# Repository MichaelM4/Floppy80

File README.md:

########################################################################

Floppy 80 for the TRS-80 Model 3/4 NGA

The Floppy80 emulates up to four floppy drives.

Configuration of the Floppy80 is performed with the placement of
files on the SD-Card inserted in its card reader.
The files are as follows:

boot.cfg
- specified the defaul ini file to load at reset of the Floppy80
  when the floppy 80 boots or is reset it reads the contents of
  the boot.cfg to determine the default configuration ini file.

ini files
- specifies the disk images to load after reset.

  ini options
  - Drive0 - specified the image to load for drive :0
  - Drive1 - specified the image to load for drive :1
  - Drive2 - specified the image to load for drive :2
  - Drive3 - specified the image to load for drive :3

dmk files
- these are virtual disk images with a specific file format
  that allows them to be generated and used with a number
  of existing programs and simulators.

hfe files
- these are virtual disk images with a specific file format
  that allows them to be generated and used with a number
  of existing programs and simulators.

########################################################################

FDC utility
- Is a utility to interact with the Floppy80 from within the
  TRS-80 Model 3/4 operating environment.  Versions of FDC exist
  for the following operating systems

  - CPM
  - LDOS
  - TRSDOS

  FDC.COM is used with the CP/M OS and
  FDC/CMD is used with the rest.

  Usage

  FDC OPT PARM1:drive

  Where:
  - OPT is one of the following
    - STA - returns the status of the Floppy80.
    - INI - switches between tyhe differnt ini file on the SD-Card.
    - DMK - allows the mounting of DMK disk images in the root folder
            of the SD-Card for a specified drive (0, 1, 2 or 3).
    - IMP - imports a file from the root folder of the SD-Card
            into one of the mounted disk images (0, 1, 2 or 3).

  FDC STA
  - Displays the contects to the ini file specified by boot.cfg

  FDC INI filename.exe
  - filename.exe is optional.  If not specified and list of ini files
    on the SD-Card will be displayed allow you to select the one to
    write to boot.cfg.  When specified FDC will bypass the file
    selection process.

  FDC DMK filename.exe n
  - filename.exe:n is optional.  When specified it will mount
    the dmk file names by filename.exe into the drive specified
    by n.  For example

    FDC DMK LDOS-DATA.DMK 2

    will mount the dmk file LDOS-DATA.DMK into drive :2

    If filename.exe:n is not specfied a list of dmk files
    will be listed allowing you to select on and the drive
    to mount it into.

  FDC IMP filename.exe:n
  - imports the specified file from the root folder of the
    FAT32 formated SD-Card to the disk image indicated by n.

########################################################################

Building Source
- Floppy80 firmware
  - Uses VSCode and the Pi Pico extension.

- FDC TRS (utility for the TRSDOS related utility)
  
  - zmac fdc.asm

- FDC CP/M (utility for the CP/M related utility)
  1. Import the source file onto a working CP/M diskette.
  
       D:\TRS-80\TRSUtils\trswrite cpm-work2.dmk -o fdc.c
     
  2. Run TRS80GP loading the CP/M disk images.
     
       start trs80gp -m4 -vs -frehd -frehd_dir source -turbo -mem 128 -d0 M4-CPM-MONTEZUMA-v22.dmk -d1 cpm-hc-disk.dmk -d2 cpm-work1.dmk -d3 cpm-work2.dmk
     
  3. Compile the C source using the Hi-Tech C compilier.

     b:
     c d:fdc.c

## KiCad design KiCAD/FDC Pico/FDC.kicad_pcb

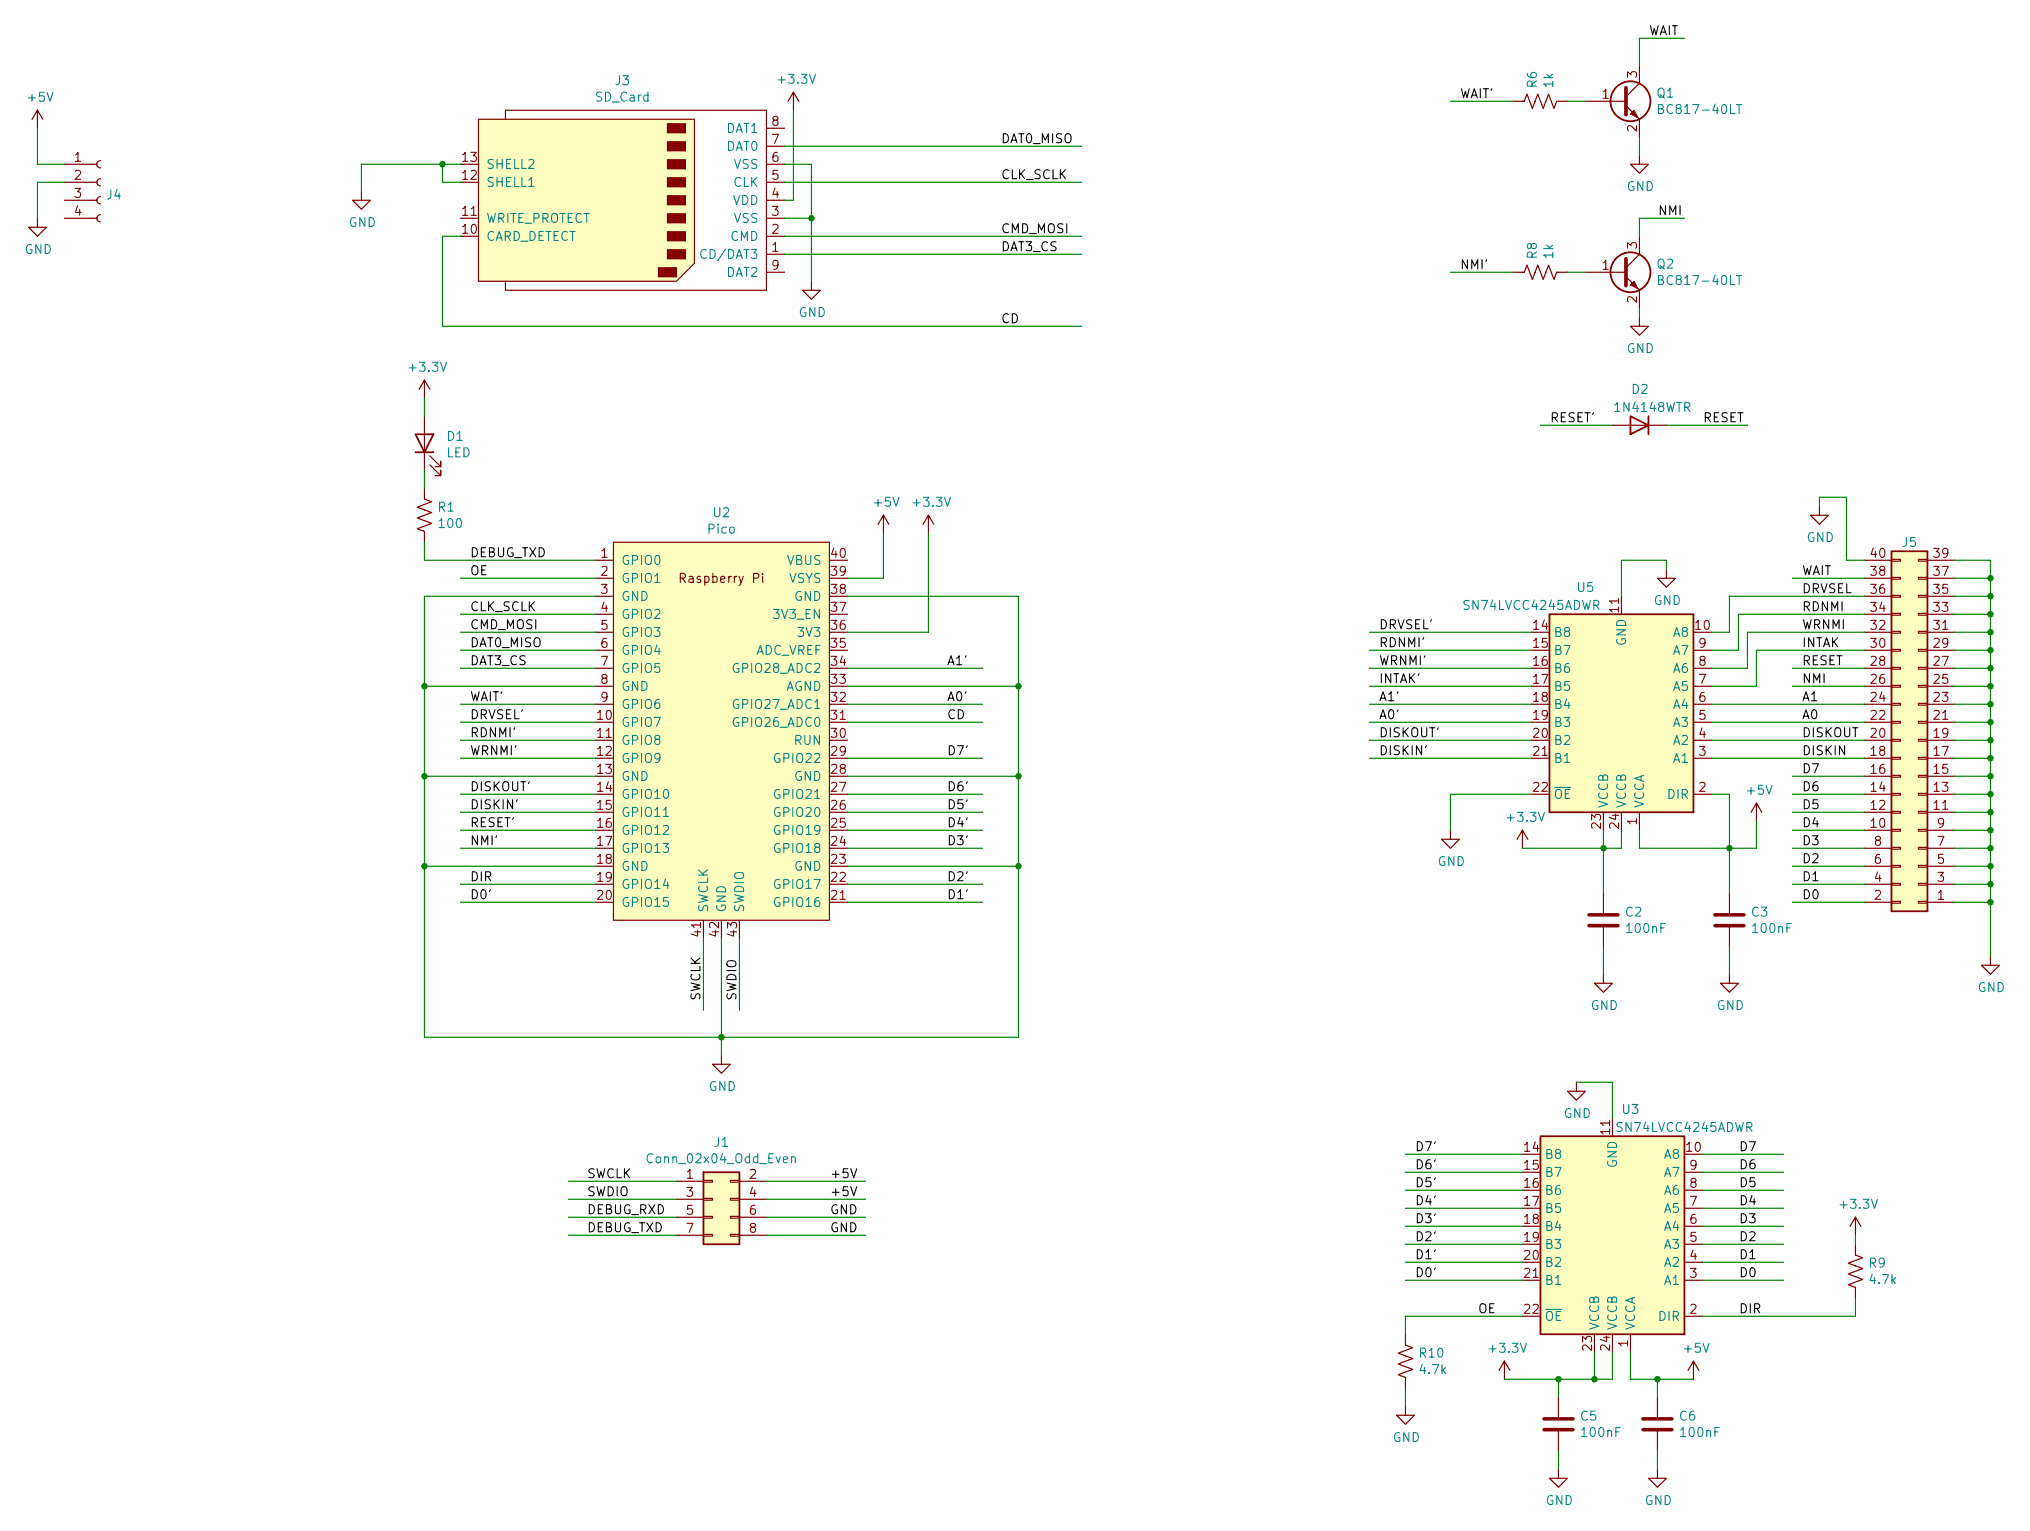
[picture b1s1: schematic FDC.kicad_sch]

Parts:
C2, C3, C5, C6: 100nF; C_0603_1608Metric_Pad1.08x0.95mm_HandSolder; Digikey 732-8080-1-ND
D1: LED; LED_2816_7142Metric_Pad3.20x4.45mm_HandSolder; Digikey 754-1519-1-ND
D2: 1N4148WTR; D_1206_3216Metric_Pad1.42x1.75mm_HandSolder; Digikey 1655-1360-1-ND
J1: Conn_02x04_Odd_Even; IDC-Header_2x04_P2.54mm_Vertical
J3: SD_Card; SD_Kyocera_145638109511859+; Digikey 478-4058-1-ND
J4: Conn_01x04_Female; TE_MATE-N-LOK_350211-1_1x04_P5.08mm_Horizontal; Digikey A25430-ND
J5: Conn_02x20_Odd_Even; PinHeader_2x20_P2.54mm_Vertical; Digikey ED10529-ND
Q1: BC817-40LT; SOT-23_Handsoldering; Digikey BC817-40LT3GOSCT-ND
Q2: BC817-40LT; SOT-23_Handsoldering; Digikey BC817-40FDICT-ND
R1: 100; R_0805_2012Metric_Pad1.20x1.40mm_HandSolder; Digikey RMCF0805FT100RCT-ND
R6, R8: 1k; R_0805_2012Metric_Pad1.20x1.40mm_HandSolder; Digikey A106056CT-ND
R9, R10: 4.7k; R_0805_2012Metric_Pad1.20x1.40mm_HandSolder; Digikey A129757CT-ND
U2: Pico; RPi_Pico_SMD_TH; Digikey 2648-SC0915CT-ND
U3, U5: SN74LVCC4245ADWR; SOIC-24W_7.5x15.4mm_P1.27mm; Digikey 296-26634-1-ND

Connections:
+3V3: C2.1, C5.1, D1.2 (A), J3.4 (VDD), R9.1, U2.36 (3V3), U3.23 (VCCB), U3.24 (VCCB), U5.23 (VCCB), U5.24 (VCCB)
+5V: C3.1, C6.1, J1.2, J1.4, J4.1, U2.39 (VSYS), U3.1 (VCCA), U5.1 (VCCA), U5.2 (DIR)
/A0: J5.22, U5.5 (A3)
/A0': U2.32 (GPIO27_ADC1), U5.19 (B3)
/A1: J5.24, U5.6 (A4)
/A1': U2.34 (GPIO28_ADC2), U5.18 (B4)
/CD: J3.10 (CARD_DETECT), U2.31 (GPIO26_ADC0)
/CLK_SCLK: J3.5 (CLK), U2.4 (GPIO2)
/CMD_MOSI: J3.2 (CMD), U2.5 (GPIO3)
/D0: J5.2, U3.3 (A1)
/D0': U2.20 (GPIO15), U3.21 (B1)
/D1: J5.4, U3.4 (A2)
/D1': U2.21 (GPIO16), U3.20 (B2)
/D2: J5.6, U3.5 (A3)
/D2': U2.22 (GPIO17), U3.19 (B3)
/D3: J5.8, U3.6 (A4)
/D3': U2.24 (GPIO18), U3.18 (B4)
/D4: J5.10, U3.7 (A5)
/D4': U2.25 (GPIO19), U3.17 (B5)
/D5: J5.12, U3.8 (A6)
/D5': U2.26 (GPIO20), U3.16 (B6)
/D6: J5.14, U3.9 (A7)
/D6': U2.27 (GPIO21), U3.15 (B7)
/D7: J5.16, U3.10 (A8)
/D7': U2.29 (GPIO22), U3.14 (B8)
/DAT0_MISO: J3.7 (DAT0), U2.6 (GPIO4)
/DAT3_CS: J3.1 (CD/DAT3), U2.7 (GPIO5)
/DEBUG_TXD: J1.7, R1.2, U2.1 (GPIO0)
/DIR: R9.2, U2.19 (GPIO14), U3.2 (DIR)
/DISKIN: J5.18, U5.3 (A1)
/DISKIN': U2.15 (GPIO11), U5.21 (B1)
/DISKOUT: J5.20, U5.4 (A2)
/DISKOUT': U2.14 (GPIO10), U5.20 (B2)
/DRVSEL: J5.36, U5.10 (A8)
/DRVSEL': U2.10 (GPIO7), U5.14 (B8)
/INTAK: J5.30, U5.7 (A5)
/NMI: J5.26, Q2.3 (C)
/NMI': R8.1, U2.17 (GPIO13)
/OE: R10.1, U2.2 (GPIO1), U3.22 (~OE)
/RDNMI: J5.34, U5.9 (A7)
/RDNMI': U2.11 (GPIO8), U5.15 (B7)
/RESET: D2.1 (K), J5.28
/RESET': D2.2 (A), U2.16 (GPIO12)
/SWCLK: J1.1, U2.41 (SWCLK)
/SWDIO: J1.3, U2.43 (SWDIO)
/WAIT: J5.38, Q1.3 (C)
/WAIT': R6.1, U2.9 (GPIO6)
/WRNMI: J5.32, U5.8 (A6)
/WRNMI': U2.12 (GPIO9), U5.16 (B6)
GND: C2.2, C3.2, C5.2, C6.2, J1.6, J1.8, J3.3 (VSS), J3.6 (VSS), J3.12 (SHELL1), J3.13 (SHELL2), J4.2, J5.1, J5.3, J5.5, J5.7, J5.9, J5.11, J5.13, J5.15, J5.17, J5.19, J5.21, J5.23, J5.25, J5.27, J5.29, J5.31, J5.33, J5.35, J5.37, J5.39, J5.40, Q1.2 (E), Q2.2 (E), R10.2, U2.3 (GND), U2.8 (GND), U2.13 (GND), U2.18 (GND), U2.23 (GND), U2.28 (GND), U2.33 (AGND), U2.38 (GND), U2.42 (GND), U3.11 (GND), U3.12 (GND), U3.13 (GND), U5.11 (GND), U5.12 (GND), U5.13 (GND), U5.22 (~OE)
unnamed: D1.1 (K), R1.1
unnamed: Q1.1 (B), R6.2
unnamed: Q2.1 (B), R8.2

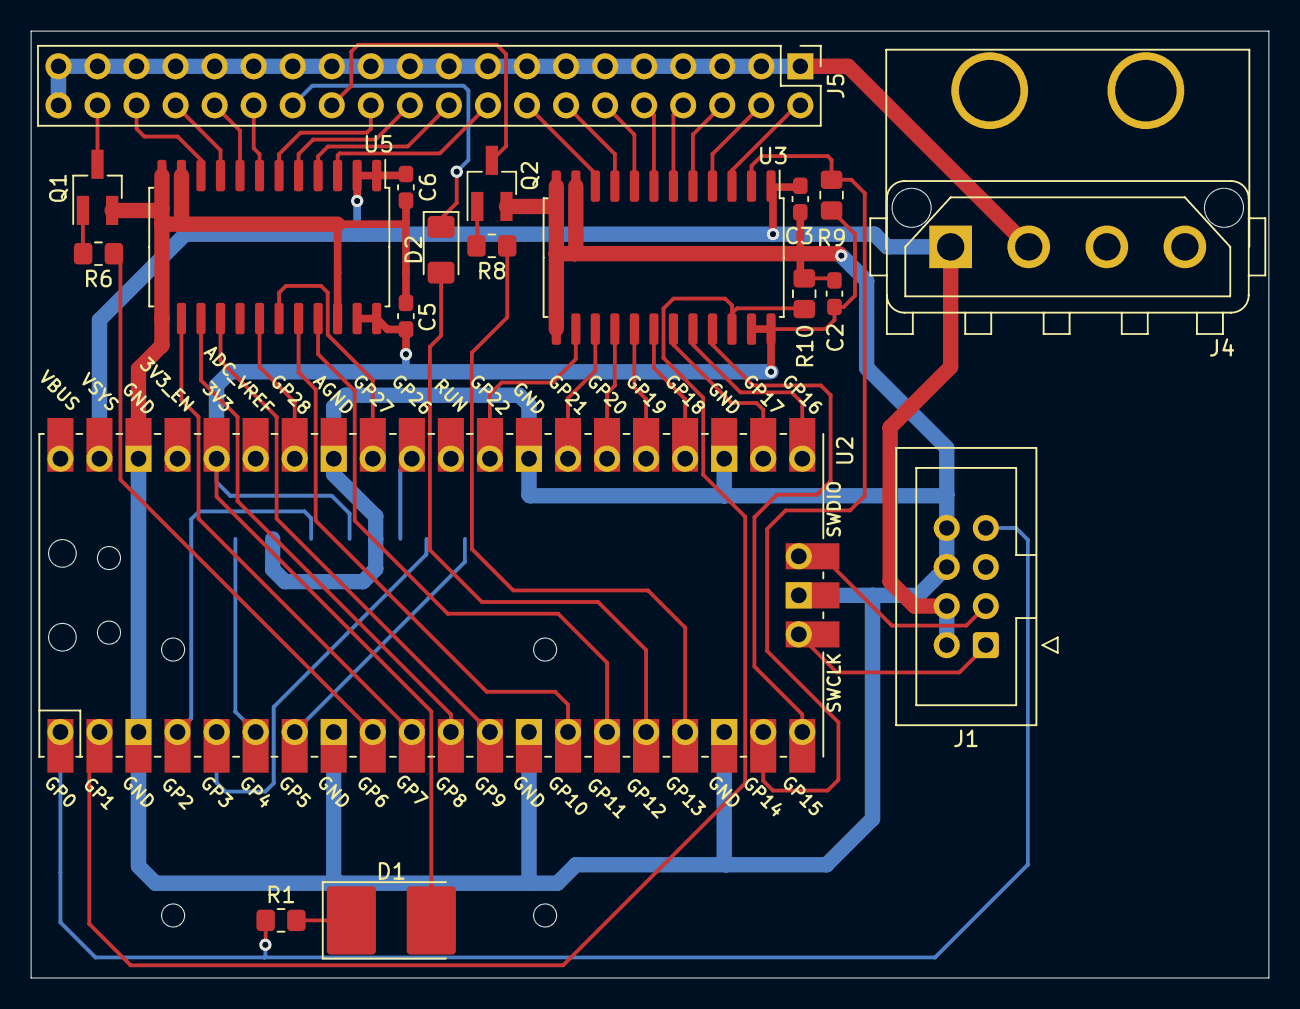
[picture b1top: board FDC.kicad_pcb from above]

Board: 2 copper layers, 80.5 x 61.6 mm, 20 parts (1 on the bottom side), 53 nets.

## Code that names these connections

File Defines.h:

#ifndef _H_DEFINES_
#define _H_DEFINES_

#include <stdio.h>

// set to 1 to enable capture of bus activity logging to sd-card
#define ENABLE_TRACE_LOG 0

///////////////////////////////////////////////////////////////////////////////////////////////////
// Bit - 31 30 29 28 27 26 25 24 23 22 21 20 19 18 17 16 15 14  13  12  11     10      9     8     7      6    5    4    3   2   1  0
// Net -          A1 A0 CD          D7 D6 D5 D4 D3 D2 D1 D0 DIR NMI RST DISKIN DISKOUT WRNMI RDNMI DRVSEL WAIT DAT3 DAT0 CMD CLK OE TXD
//       0  0  0  1  1  1  0  0  0  1  1  1  1  1  1  1  1  0   0   1   1      1       1     1     1      0    0    0    0   0   0  0
//       ----------  ----------  ----------  ----------  ------------   ----------------------     ------------------    ------------
// Hex            1           C           7           F             9                        F                      8               0
#define GPIO_IN_MASK 0x1C7F9F80

#define DRVSEL_MASK   0x00000080
#define RDNMI_MASK    0x00000100
#define WRNMI_MASK    0x00000200
#define DISKOUT_MASK  0x00000400
#define DISKIN_MASK   0x00000800

#define INTR_MASK     (DRVSEL_MASK | RDNMI_MASK | WRNMI_MASK | DISKOUT_MASK | DISKIN_MASK)

#define ADDRESS_MASK  0x18000000
#define DATA_BUS_MASK 0x007F8000

#define NMI_MASK      0x00002000
#define WAIT_MASK     0x00000040

#define RED_LED_PIN 0
#define OE_PIN      1
#define CLK_SCLK    2
#define CMD_MOSI    3
#define DAT0_MISO   4
#define DAT3_CS     5

#define WAIT_PIN    6
#define DRVSEL_PIN  7
#define RDNMI_PIN   8
#define WRNMI_PIN   9
#define DISKOUT_PIN 10
#define DISKIN_PIN  11

#define RESET_PIN   12
#define NMI_PIN     13
#define DIR_PIN     14

#define D0_PIN      15
#define D1_PIN      16
#define D2_PIN      17
#define D3_PIN      18
#define D4_PIN      19
#define D5_PIN      20
#define D6_PIN      21
#define D7_PIN      22

#define CD_PIN      26

#define A0_PIN      27
#define A1_PIN      28

#define DIR_PIN_MASK  0x4000

///////////////////////////////////////////////////////////////////////////////////////////////////

#define BOARD_REVISION 2

extern int g_nRevBoard;

///////////////////////////////////////////////////////////////////////////////////////////////////

// Low Power Timer Overflow Rates in Hz
#define TIMER_OVERFLOW_RATE				2000

///////////////////////////////////////////////////////////////////////////////////////////////////
// generic defines/equates

#ifndef TRUE
	#define FALSE	0
	#define TRUE	1
#endif

///////////////////////////////////////////////////////////////////////////////////////////////////
// typedefs

typedef long long          	INT64;
typedef unsigned long long 	UINT64;
typedef unsigned long      	UINT32;
typedef long               	INT32;
typedef unsigned short     	UINT16;
typedef short              	INT16;
typedef unsigned char		    UINT8;
typedef signed char        	INT8;
typedef signed char        	SCHAR;
typedef unsigned long      	DWORD;
typedef unsigned short     	WORD;
typedef unsigned char      	BYTE;
typedef char		       	    CHAR;

typedef struct {
   unsigned long long nSectorsTotal;
   unsigned long long nSectorsFree;
   unsigned long long nSectorSize;

   unsigned long nClustersTotal;
   unsigned long nClustersFree;
   unsigned long nClustersUsed;
   unsigned long nClustersBad;
   unsigned long nClusterSize;
} F_SPACE;

typedef union
{
  struct
  {
    // note that this is valid only if the GPIO all input is rotated down 6 bits
    // in reality WAIT is at GPIO6
    uint32_t WAIT:1;                     /*!< bit:  0      WAIT                               */
    uint32_t DVRSEL:1;                   /*!< bit:  1      DRIVESEL                           */
    uint32_t RDNMI:1;                    /*!< bit:  2      RDNMISTATUS                        */
    uint32_t WRNMI:1;                    /*!< bit:  3      WRNMIMASKREG                       */
    uint32_t DISK_OUT_WE:1;              /*!< bit:  4      DISK_OUT                           */
    uint32_t DISK_IN_RE:1;               /*!< bit:  5      DISK_IN                            */
    uint32_t RESET:1;                    /*!< bit:  6      RESET                              */
    uint32_t NMI:1;                      /*!< bit:  7      NMI                                */
    uint32_t DIR:1;                      /*!< bit:  8      DIR                                */
    uint32_t DATA:8;                     /*!< bit:  9..16  Data Bus                           */

    uint32_t NA2:3;                      /*!< bit:  17..19 NA                                 */
    uint32_t CD:1;                       /*!< bit:  20     CD                                 */
    uint32_t A0:1;                       /*!< bit:  21     A0                                 */
    uint32_t A1:1;                       /*!< bit:  22     A1                                 */

    uint32_t Count:9;                    /*!< bit:  23..31 Count                              */
  } b;                                   /*!< Structure used for bit  access                  */
  uint32_t dw;                           /*!< Type      used for word access                  */
} FDC_BusBitsType;

typedef struct {
	FDC_BusBitsType Bus;
  uint32_t        dwTicks;
} FDC_BusType;

///////////////////////////////////////////////////////////////////////////////////////////////////
// enumerations

enum PowerModes
{
	ccNormal   = 1,
	ccLowPower = 2,
};

void ConfigureCoreClock(int nClockOption);

///////////////////////////////////////////////////////////////////////////////////////////////////
// global variables

//-----------------------------------------------------------------------------
// counter for real time clock (RTC).

extern DWORD g_dwForegroundRtc;
extern DWORD g_dwBackgroundRtc;
extern WORD  g_wWatchdogRefreshCounter;
extern DWORD g_dwRTC;

extern BYTE  g_byCaptureBusActivity;

extern DWORD g_dwRotationTime;
extern DWORD g_dwIndexTime;
extern DWORD g_dwResetTime;

extern BYTE  g_byMonitorReset;

extern uint64_t g_nWaitTime;
extern uint64_t g_nTimeStart;
extern uint64_t g_nTimeEnd;
extern uint64_t g_nTimeDiff;

///////////////////////////////////////////////////////////////////////////////////////////////////

void TogglePin(int nCount);
void InitVars(void);
void DecodeBusData(FDC_BusType* pHistory, char* psz, int nType);
void ReleaseWait(void);

///////////////////////////////////////////////////////////////////////////////////////////////////

DWORD CalcDuration(DWORD dwEndCount, DWORD dwStartCount);
void  InitBusTrace(void);
void  FlushTraceBuffer(void);

///////////////////////////////////////////////////////////////////////////////////////////////////

#endif

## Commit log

2022-09-19 First commit to github
2025-11-07 Removes build folder that should not have been part of the original repository.
2025-11-07 Adds KiCAD PCB design files.
